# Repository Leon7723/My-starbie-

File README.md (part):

this is my first hardware proyect, im making a desktop pet or something like a tamagothi and is looking pretty good, im making this proyect for half life in hackclub my goal is to win that 3d printer but my number 1 goal is to learn how to make hardware proyects by my own :D

here is the files than i made:
{
  "board": {
    "3dviewports": [],
    "design_settings": {
      "defaults": {
        "apply_defaults_to_fp_barcodes": false,
        "apply_defaults_to_fp_dimensions": false,
        "apply_defaults_to_fp_fields": false,
        "apply_defaults_to_fp_shapes": false,
        "apply_defaults_to_fp_text": false,
        "board_outline_line_width": 0.05,
        "copper_line_width": 0.2,
        "copper_text_italic": false,
        "copper_text_size_h": 1.5,
        "copper_text_size_v": 1.5,
        "copper_text_thickness": 0.3,
        "copper_text_upright": false,
        "courtyard_line_width": 0.05,
        "dimension_precision": 4,
        "dimension_units": 3,
        "dimensions": {
          "arrow_length": 1270000,
          "extension_offset": 500000,
          "keep_text_aligned": true,
          "suppress_zeroes": true,
          "text_position": 0,
          "units_format": 0
        },
        "fab_line_width": 0.1,
        "fab_text_italic": false,
        "fab_text_size_h": 1.0,
        "fab_text_size_v": 1.0,
        "fab_text_thickness": 0.15,
        "fab_text_upright": false,
        "other_line_width": 0.1,
        "other_text_italic": false,
        "other_text_size_h": 1.0,
        "other_text_size_v": 1.0,
        "other_text_thickness": 0.15,
        "other_text_upright": false,
        "pads": {
          "drill": 0.8,
          "height": 1.27,
          "width": 1.27
        },
        "silk_line_width": 0.1,
        "silk_text_italic": false,
        "silk_text_size_h": 1.0,
        "silk_text_size_v": 1.0,
        "silk_text_thickness": 0.1,
        "silk_text_upright": false,
        "zones": {
          "border_display_style": 2,
          "border_hatch_pitch": 0.5,
          "corner_radius": 0.0,
          "corner_smoothing": 0,
          "fill_mode": 0,
          "hatch_gap": 1.5,
          "hatch_orientation": 0.0,
          "hatch_smoothing_level": 0,
          "hatch_smoothing_value": 0.1,
          "hatch_thickness": 1.0,
          "min_clearance": 0.5,
          "min_island_area": 10.0,
          "min_thickness": 0.25,
          "pad_connection": 1,
          "remove_islands": 0,
          "thermal_relief_gap": 0.5,
          "thermal_relief_spoke_width": 0.5
        }
      },
      "diff_pair_dimensions": [],
      "drc_exclusions": [],
      "meta": {
        "version": 2
      },
      "rule_severities": {
        "annular_width": "error",
        "clearance": "error",
        "connection_width": "warning",
        "copper_edge_clearance": "error",
        "copper_sliver": "warning",
        "courtyards_overlap": "error",
        "creepage": "error",
        "diff_pair_gap_out_of_range": "error",
        "diff_pair_uncoupled_length_too_long": "error",
        "drill_out_of_range": "error",
        "duplicate_footprints": "warning",
        "extra_footprint": "warning",
        "footprint": "error",
        "footprint_filters_mismatch": "ignore",
        "footprint_symbol_field_mismatch": "warning",
        "footprint_symbol_mismatch": "warning",
        "footprint_type_mismatch": "ignore",
        "hole_clearance": "error",
        "hole_to_hole": "warning",
        "holes_co_located": "warning",
        "invalid_outline": "error",
        "isolated_copper": "warning",
        "item_on_disabled_layer": "error",
        "items_not_allowed": "error",
        "length_out_of_range": "error",
        "lib_footprint_issues": "warning",
        "lib_footprint_mismatch": "warning",
        "malformed_courtyard": "error",
        "microvia_drill_out_of_range": "error",
        "mirrored_text_on_front_layer": "warning",
        "missing_courtyard": "ignore",
        "missing_footprint": "warning",
        "missing_tuning_profile": "warning",
        "net_conflict": "warning",
        "nonmirrored_text_on_back_layer": "warning",
        "npth_inside_courtyard": "error",
        "padstack": "warning",
        "pth_inside_courtyard": "error",
        "shorting_items": "error",
        "silk_edge_clearance": "warning",
        "silk_over_copper": "warning",
        "silk_overlap": "warning",
        "skew_out_of_range": "error",
        "solder_mask_bridge": "error",
        "starved_thermal": "error",
        "text_height": "warning",
        "text_on_edge_cuts": "error",
        "text_thickness": "warning",
        "through_hole_pad_without_hole": "error",
        "too_many_vias": "error",
        "track_angle": "error",
        "track_dangling": "warning",
        "track_not_centered_on_via": "ignore",
        "track_on_post_machined_layer": "error",
        "track_segment_length": "error",
        "track_width": "error",
        "tracks_crossing": "error",
        "tuning_profile_track_geometries": "ignore",
        "unconnected_items": "error",
        "unresolved_variable": "error",
        "via_dangling": "warning",
        "zones_intersect": "error"
      },
      "rules": {
        "max_error": 0.005,
        "min_clearance": 0.0,
        "min_connection": 0.0,
        "min_copper_edge_clearance": 0.5,
        "min_groove_width": 0.0,
        "min_hole_clearance": 0.25,
        "min_hole_to_hole": 0.25,
        "min_microvia_diameter": 0.2,
        "min_microvia_drill": 0.1,
        "min_resolved_spokes": 2,
        "min_silk_clearance": 0.0,
        "min_text_height": 0.8,
        "min_text_thickness": 0.08,
        "min_through_hole_diameter": 0.3,
        "min_track_width": 0.2,
        "min_via_annular_width": 0.1,
        "min_via_diameter": 0.5,
        "solder_mask_to_copper_clearance": 0.0,
        "use_height_for_length_calcs": true
      },
      "teardrop_options": [
        {
          "td_onpthpad": true,
          "td_onroundshapesonly": false,
          "td_onsmdpad": true,
          "td_ontrackend": false,
          "td_onvia": true
        }
      ],
      "teardrop_parameters": [
        {
          "td_allow_use_two_tracks": true,
          "td_curve_segcount": 0,
          "td_height_ratio": 1.0,
          "td_length_ratio": 0.5,
          "td_maxheight": 2.0,
          "td_maxlen": 1.0,
          "td_on_pad_in_zone": false,
          "td_target_name": "td_round_shape",
          "td_width_to_size_filter_ratio": 0.9
        },
        {
          "td_allow_use_two_tracks": true,
          "td_curve_segcount": 0,
          "td_height_ratio": 1.0,
          "td_length_ratio": 0.5,
          "td_maxheight": 2.0,
          "td_maxlen": 1.0,
          "td_on_pad_in_zone": false,
          "td_target_name": "td_rect_shape",
          "td_width_to_size_filter_ratio": 0.9
        },
        {
          "td_allow_use_two_tracks": true,
          "td_curve_segcount": 0,
          "td_height_ratio": 1.0,
          "td_length_ratio": 0.5,
          "td_maxheight": 2.0,
          "td_maxlen": 1.0,
          "td_on_pad_in_zone": false,
          "td_target_name": "td_track_end",
          "td_width_to_size_filter_ratio": 0.9
        }
      ],
      "track_widths": [],
      "tuning_pattern_settings": {
        "diff_pair_defaults": {
          "corner_radius_percentage": 80,
          "corner_style": 1,
          "max_amplitude": 1.0,
          "min_amplitude": 0.2,
          "single_sided": false,
          "spacing": 1.0
        },
        "diff_pair_skew_defaults": {
          "corner_radius_percentage": 80,
          "corner_style": 1,
          "max_amplitude": 1.0,
          "min_amplitude": 0.2,
          "single_sided": false,
          "spacing": 0.6
        },
        "single_track_defaults": {
          "corner_radius_percentage": 80,
          "corner_style": 1,
          "max_amplitude": 1.0,
          "min_amplitude": 0.2,
          "single_sided": false,
          "spacing": 0.6
        }
      },
      "via_dimensions": [],
      "zones_allow_external_fillets": false
    },
    "ipc2581": {
      "bom_rev": "",
      "dist": "",
      "distpn": "",
      "internal_id": "",
      "mfg": "",
      "mpn": "",
      "sch_revision": ""
    },
    "layer_pairs": [],
    "layer_presets": [],
    "viewports": []
  },
  "boards": [],
  "component_class_settings": {
    "assignments": [],
    "meta": {
      "version": 0
    },
    "sheet_component_classes": {
      "enabled": false
    }
  },
  "cvpcb": {
    "equivalence_files": []
  },
  "erc": {
    "erc_exclusions": [],
    "meta": {
      "version": 0
    },
    "pin_map": [
      [
        0,
        0,
        0,
        0,
        0,
        0,
        1,
        0,
        0,
        0,
        0,
        2
      ],
      [
        0,
        2,
        0,
        1,
        0,
        0,
        1,
        0,
        2,
        2,
        2,
        2
      ],
      [
        0,
        0,
        0,
        0,
        0,
        0,
        1,
        0,
        1,
        0,
        1,
        2
      ],
      [
        0,
        1,
        0,
        0,
        0,
        0,
        1,
        1,
        2,
        1,
        1,
        2
      ],
      [
        0,
        0,
        0,
        0,
        0,
        0,
        1,
        0,
        0,
        0,
        0,
        2
      ],
      [
        0,
        0,
        0,
        0,
        0,
        0,
        0,
        0,
        0,
        0,
        0,
        2
      ],
      [
        1,
        1,
        1,
        1,
        1,
        0,
        1,
        1,
        1,
        1,
        1,
        2
      ],
      [
        0,
        0,
        0,
        1,
        0,
        0,
        1,
        0,
        0,
        0,
        0,
        2
      ],
      [
        0,
        2,
        1,
        2,
        0,
        0,
        1,
        0,
        2,
        2,
        2,
        2
      ],
      [
        0,
        2,
        0,
        1,
        0,
        0,
        1,
        0,
        2,
        0,
        0,
        2
      ],
      [
        0,
        2,
        1,
        1,
        0,
        0,
        1,
        0,
        2,
        0,
        0,
        2
      ],
      [
        2,
        2,
        2,
        2,
        2,
        2,
        2,
        2,
        2,
        2,
        2,
        2
      ]
    ],
    "rule_severities": {
      "bus_definition_conflict": "error",
      "bus_entry_needed": "error",
      "bus_to_bus_conflict": "error",
      "bus_to_net_conflict": "error",
      "different_unit_footprint": "error",
      "different_unit_net": "error",
      "duplicate_reference": "error",
      "duplicate_sheet_names": "error",
      "endpoint_off_grid": "warning",
      "extra_units": "error",
      "field_name_whitespace": "warning",
      "footprint_filter": "ignore",
      "footprint_link_issues": "warning",
      "four_way_junction": "ignore",
      "ground_pin_not_ground": "warning",
      "hier_label_mismatch": "error",
      "isolated_pin_label": "warning",
      "label_dangling": "error",
      "label_multiple_wires": "warning",
      "lib_symbol_issues": "warning",
      "lib_symbol_mismatch": "warning",
      "missing_bidi_pin": "warning",
      "missing_input_pin": "warning",
      "missing_power_pin": "error",
      "missing_unit": "warning",
      "multiple_net_names": "warning",
      "net_not_bus_member": "warning",
      "no_connect_connected": "warning",
      "no_connect_dangling": "warning",
      "pin_not_connected": "error",
      "pin_not_driven": "error",
      "pin_to_pin": "warning",
      "power_pin_not_driven": "error",
      "same_local_global_label": "warning",
      "similar_label_and_power": "warning",
      "similar_labels": "warning",
      "similar_power": "warning",
      "simulation_model_issue": "ignore",
      "single_global_label": "ignore",
      "stacked_pin_name": "warning",
      "unannotated": "error",
      "unconnected_wire_endpoint": "warning",
      "undefined_netclass": "error",
      "unit_value_mismatch": "error",
      "unresolved_variable": "error",
      "wire_dangling": "error"
    }
  },
  "libraries": {
    "pinned_footprint_libs": [],
    "pinned_symbol_libs": []
  },
  "meta": {
    "filename": "starbie.kicad_pro",
    "version": 3
  },
  "net_settings": {
    "classes": [
      {
        "bus_width": 12,
        "clearance": 0.2,
        "diff_pair_gap": 0.25,
        "diff_pair_via_gap": 0.25,
        "diff_pair_width": 0.2,
        "line_style": 0,
        "microvia_diameter": 0.3,
        "microvia_drill": 0.1,
        "name": "Default",
        "pcb_color": "rgba(0, 0, 0, 0.000)",
        "priority": 2147483647,
        "schematic_color": "rgba(0, 0, 0, 0.000)",
        "track_width": 0.2,
        "tuning_profile": "",
        "via_diameter": 0.6,
        "via_drill": 0.3,
        "wire_width": 6
      }
    ],
    "meta": {
      "version": 5
    },
    "net_colors": null,
    "netclass_assignments": null,
    "netclass_patterns": []
  },
  "pcbnew": {
    "last_paths": {
      "idf": "",
      "netlist": "",
      "plot": "",
      "specctra_dsn": "",
      "step": "",
      "vrml": ""
    },
    "page_layout_descr_file": ""
  },
  "schematic": {
    "annotate_start_num": 0,
    "annotation": {
      "method": 0,
      "sort_order": 0
    },
    "bom_export_filename": "${PROJECTNAME}.csv",
    "bom_fmt_presets": [],
    "bom_fmt_settings": {
      "field_delimiter": ",",
      "keep_line_breaks": false,
      "keep_tabs": false,
      "name": "CSV",
      "ref_delimiter": ",",
      "ref_range_delimiter": "",
      "string_delimiter": "\""
    },
    "bom_presets": [],
    "bom_settings": {
      "exclude_dnp": false,
      "fields_ordered": [
        {
          "group_by": false,
          "label": "Reference",
          "name": "Reference",
          "show": true
        },
        {
          "group_by": false,
          "label": "Qty",
          "name": "${QUANTITY}",
          "show": true
        },
        {
          "group_by": true,
          "label": "Value",
          "name": "Value",
          "show": true
        },
        {
          "group_by": true,
          "label": "DNP",
          "name": "${DNP}",
          "show": true
        },
        {
          "group_by": true,
          "label": "Exclude from BOM",
          "name": "${EXCLUDE_FROM_BOM}",
          "show": true
        },
        {
          "group_by": true,
          "label": "Exclude from Board",
          "name": "${EXCLUDE_FROM_BOARD}",
          "show": true
        },
        {
          "group_by": true,
          "label": "Exclude from Simulation",
          "name": "${EXCLUDE_FROM_SIM}",
          "show": true
        },
        {
          "group_by": true,
          "label": "Exclude from Position Files",
          "name": "${EXCLUDE_FROM_POS_FILES}",
          "show": true
        },
        {
          "group_by": true,
          "label": "Footprint",
          "name": "Footprint",
          "show": true
        },
        {
          "group_by": false,
          "label": "Datasheet",
          "name": "Datasheet",
          "show": true
        }
      ],
      "filter_string": "",
      "group_symbols": true,
      "include_excluded_from_bom": true,
      "name": "Default Editing",
      "sort_asc": true,
      "sort_field": "Reference"
    },
    "bus_aliases": {},
    "connection_grid_size": 50.0,
    "drawing": {
      "dashed_lines_dash_length_ratio": 12.0,
      "dashed_lines_gap_length_ratio": 3.0,
      "default_line_thickness": 6.0,
      "default_text_size": 50.0,
      "field_names": [],
      "hop_over_size_choice": 0,
      "intersheets_ref_own_page": false,
      "intersheets_ref_prefix": "",
      "intersheets_ref_short": false,
      "intersheets_ref_show": false,
      "intersheets_ref_suffix": "",
      "junction_size_choice": 3,
      "label_size_ratio": 0.375,
      "operating_point_overlay_i_precision": 3,
      "operating_point_overlay_i_range": "~A",
      "operating_point_overlay_v_precision": 3,
      "operating_point_overlay_v_range": "~V",
      "overbar_offset_ratio": 1.23,
      "pin_symbol_size": 25.0,
      "text_offset_ratio": 0.15
    },
    "legacy_lib_dir": "",
    "legacy_lib_list": [],
    "meta": {
      "version": 1
    },
    "page_layout_descr_file": "",
    "plot_directory": "",
    "reuse_designators": true,
    "subpart_first_id": 65,
    "subpart_id_separator": 0,
    "top_level_sheets": [
      {
        "filename": "starbie.kicad_sch",
        "name": "Root",
        "uuid": "8977db72-0acb-4ad4-afa3-dd83609eab31"
      }
    ],
    "used_designators": "U1-2,SW1-2,R1,J1-2,#PWR1-13",
    "variants": []
  },
  "sheets": [
    [
      "8977db72-0acb-4ad4-afa3-dd83609eab31",
      "Root"
    ]
  ],
  "text_variables": {},
  "tuning_profiles": {
    "meta": {
      "version": 0
    },
    "tuning_profiles_impedance_geometric": []
  }
}

(kicad_pcb
	(version 20260206)
	(generator "pcbnew")
	(generator_version "10.0")
	(general
		(thickness 1.6)
		(legacy_teardrops no)
	)
	(paper "A4")
	(layers
		(0 "F.Cu" signal)
		(2 "B.Cu" signal)
		(9 "F.Adhes" user "F.Adhesive")
		(11 "B.Adhes" user "B.Adhesive")
		(13 "F.Paste" user)
		(15 "B.Paste" user)
		(5 "F.SilkS" user "F.Silkscreen")
		(7 "B.SilkS" user "B.Silkscreen")
		(1 "F.Mask" user)
		(3 "B.Mask" user)
		(17 "Dwgs.User" user "User.Drawings")
		(19 "Cmts.User" user "User.Comments")
		(21 "Eco1.User" user "User.Eco1")
		(23 "Eco2.User" user "User.Eco2")
		(25 "Edge.Cuts" user)
		(27 "Margin" user)
		(31 "F.CrtYd" user "F.Courtyard")
		(29 "B.CrtYd" user "B.Courtyard")
		(35 "F.Fab" user)
		(33 "B.Fab" user)
		(39 "User.1" user)
		(41 "User.2" user)
		(43 "User.3" user)
		(45 "User.4" user)
	)
	(setup
		(pad_to_mask_clearance 0)
		(allow_soldermask_bridges_in_footprints no)
		(tenting
			(front yes)
			(back yes)
		)
		(covering
			(front no)
			(back no)
		)
		(plugging
			(front no)
			(back no)
		)
		(capping no)
		(filling no)
		(pcbplotparams
			(layerselection 0x00000000_00000000_55555555_5755f5ff)
			(plot_on_all_layers_selection 0x00000000_00000000_00000000_00000000)
			(disableapertmacros no)
			(usegerberextensions no)
			(usegerberattributes yes)
			(usegerberadvancedattributes yes)
			(creategerberjobfile yes)
			(dashed_line_dash_ratio 12)
			(dashed_line_gap_ratio 3)
			(svgprecision 4)
			(plotframeref no)
			(mode 1)
			(useauxorigin no)
			(pdf_front_fp_property_popups yes)
			(pdf_back_fp_property_popups yes)
			(pdf_metadata yes)
			(pdf_single_document no)
			(dxfpolygonmode yes)
			(dxfimperialunits yes)
			(dxfusepcbnewfont yes)
			(psnegative no)
			(psa4output no)
			(plot_black_and_white yes)
			(sketchpadsonfab no)
			(plotpadnumbers no)
			(hidednponfab no)
			(sketchdnponfab yes)
			(crossoutdnponfab yes)
			(subtractmaskfromsilk no)
			(outputformat 1)
			(mirror no)
			(drillshape 1)
			(scaleselection 1)
			(outputdirectory "")
		)
	)
	(footprint "Button_Switch_Keyboard:SW_Cherry_MX_1.00u_PCB"
		(layer "F.Cu")
		(uuid "04947574-7416-4cc5-8b59-ddabbcdf914b")
		(at 125.96 61.42)
		(descr "Cherry MX keyswitch, 1.00u, PCB mount, http://cherryamericas.com/wp-content/uploads/2014/12/mx_cat.pdf")
		(tags "Cherry MX keyswitch 1.00u PCB")
		(property "Reference" "SW1"
			(at -2.54 -2.794 0)
			(layer "F.SilkS")
			(uuid "132addf6-2cf2-4cc4-88fb-be52d615f856")
			(effects
				(font
					(size 1 1)
					(thickness 0.15)
				)
			)
		)
		(property "Value" "SW_Push"
			(at -2.54 12.954 0)
			(layer "F.Fab")
			(uuid "f20ce212-0395-475c-ab5a-2ed35deecf76")
			(effects
				(font
					(size 1 1)
					(thickness 0.15)
				)
			)
		)
		(property "Datasheet" ""
			(at 0 0 0)
			(unlocked yes)
			(layer "F.Fab")
			(hide yes)
			(uuid "22c549e9-61a7-43be-9221-d960f5cf3cf2")
			(effects
				(font
					(size 1.27 1.27)
					(thickness 0.15)
				)
			)
		)
		(property "Description" "Push button switch, generic, two pins"
			(at 0 0 0)
			(unlocked yes)
			(layer "F.Fab")
			(hide yes)
			(uuid "7d2f7fe1-6565-423b-a553-d9594f436d74")
			(effects
				(font
					(size 1.27 1.27)
					(thickness 0.15)
				)
			)
		)
		(path "/6c2d0e86-b1ff-40f8-8c9f-153c65c3ee15")
		(sheetname "/")
		(sheetfile "starbie.kicad_sch")
		(units
			(unit
				(name "A")
				(pins "1" "2")
			)
		)
		(attr through_hole)
		(duplicate_pad_numbers_are_jumpers no)
		(fp_line
			(start -9.525 -1.905)
			(end 4.445 -1.905)
			(stroke
				(width 0.12)
				(type solid)
			)
			(layer "F.SilkS")
			(uuid "a28ee2ab-d00a-4bbe-a005-b5f784556526")
		)
		(fp_line
			(start -9.525 12.065)
			(end -9.525 -1.905)
			(stroke
				(width 0.12)
				(type solid)
			)
			(layer "F.SilkS")
			(uuid "6eea82b2-2c50-4da5-b7d3-b83acb185266")
		)
		(fp_line
			(start 4.445 -1.905)
			(end 4.445 12.065)
			(stroke
				(width 0.12)
				(type solid)
			)
			(layer "F.SilkS")
			(uuid "b50e151d-3af0-442f-9106-87fc13568458")
		)
		(fp_line
			(start 4.445 12.065)
			(end -9.525 12.065)
			(stroke
				(width 0.12)
				(type solid)
			)
			(layer "F.SilkS")
			(uuid "75a63ca7-dc22-4e55-95bc-e4980ed241a7")
		)
		(fp_line
			(start -12.065 -4.445)
			(end 6.985 -4.445)
			(stroke
				(width 0.15)
				(type solid)
			)
			(layer "Dwgs.User")
			(uuid "a4316273-7a1b-420c-a8fc-29acb0b7fac4")
		)
		(fp_line
			(start -12.065 14.605)
			(end -12.065 -4.445)
			(stroke
				(width 0.15)
				(type solid)
			)
			(layer "Dwgs.User")
			(uuid "78c734cc-3ac1-4bcd-8f04-a0f06144b939")
		)
		(fp_line
			(start 6.985 -4.445)
			(end 6.985 14.605)
			(stroke
				(width 0.15)
				(type solid)
			)
			(layer "Dwgs.User")
			(uuid "d065de42-0f82-4f18-80ed-cecb038134eb")
		)
		(fp_line
			(start 6.985 14.605)
			(end -12.065 14.605)
			(stroke
				(width 0.15)
				(type solid)
			)
			(layer "Dwgs.User")
			(uuid "ddfaa2da-c5e8-4b48-80f8-5292d8794895")
		)
		(fp_line
			(start -9.14 -1.52)
			(end 4.06 -1.52)
			(stroke
				(width 0.05)
				(type solid)
			)
			(layer "F.CrtYd")
			(uuid "9c98e6c3-9128-4f0e-b70b-2670f6951c46")
		)
		(fp_line
			(start -9.14 11.68)
			(end -9.14 -1.52)
			(stroke
				(width 0.05)
				(type solid)
			)
			(layer "F.CrtYd")
			(uuid "39c0d82c-ac3e-4125-89c2-3e9910a38456")
		)
		(fp_line
			(start 4.06 -1.52)
			(end 4.06 11.68)
			(stroke
				(width 0.05)
				(type solid)
			)
			(layer "F.CrtYd")
			(uuid "b3e67ae2-3ecd-4883-a7f6-076ef99d186b")
		)
		(fp_line
			(start 4.06 11.68)
			(end -9.14 11.68)
			(stroke
				(width 0.05)
				(type solid)
			)
			(layer "F.CrtYd")
			(uuid "a4c458d3-c2e1-4908-849c-2d97809b41e4")
		)
		(fp_line
			(start -8.89 -1.27)
			(end 3.81 -1.27)
			(stroke
				(width 0.1)
				(type solid)
			)
			(layer "F.Fab")
			(uuid "18de7187-ac3b-49d3-a1f6-a358b98e4163")
		)
		(fp_line
			(start -8.89 11.43)
			(end -8.89 -1.27)
			(stroke
				(width 0.1)
				(type solid)
			)
			(layer "F.Fab")
			(uuid "33423380-56ce-4d9c-a48a-4f5b19c81899")
		)
		(fp_line
			(start 3.81 -1.27)
			(end 3.81 11.43)
			(stroke
				(width 0.1)
				(type solid)
			)
			(layer "F.Fab")
			(uuid "1b672b95-718c-470c-9bc7-e3b12f699fa5")
		)
		(fp_line
			(start 3.81 11.43)
			(end -8.89 11.43)
			(stroke
				(width 0.1)
				(type solid)
			)
			(layer "F.Fab")
			(uuid "b3a7395a-ab9d-47c4-adad-9ad8906270ee")
		)
		(fp_text user "${REFERENCE}"
			(at -2.54 -2.794 0)
			(layer "F.Fab")
			(uuid "7bf67fcc-76aa-45bc-806b-e6e624cb3fed")
			(effects
				(font
					(size 1 1)
					(thickness 0.15)
				)
			)
		)
		(pad "" np_thru_hole circle
			(at -7.62 5.08)
			(size 1.7 1.7)
			(drill 1.7)
			(layers "*.Cu" "*.Mask")
			(uuid "2e3083d1-e926-470d-80b4-f84540161596")
		)
		(pad "" np_thru_hole circle
			(at -2.54 5.08)
			(size 4 4)
			(drill 4)
			(layers "*.Cu" "*.Mask")
			(uuid "16aa3495-d0af-4f73-a243-1d8c19ad124a")
		)
		(pad "" np_thru_hole circle
			(at 2.54 5.08)
			(size 1.7 1.7)
			(drill 1.7)
			(layers "*.Cu" "*.Mask")
			(uuid "94529e87-416b-46bd-9648-98cffbd182bb")
		)
		(pad "1" thru_hole circle
			(at 0 0)
			(size 2.2 2.2)
			(drill 1.5)
			(layers "*.Cu" "*.Mask")
			(remove_unused_layers no)
			(net "/GPIO2")
			(pinfunction "1_1")
			(pintype "passive")
			(uuid "81945a4a-24d3-4cf3-a907-b8f6f99d8b53")
		)
		(pad "2" thru_hole circle
			(at -6.35 2.54)
			(size 2.2 2.2)
			(drill 1.5)
			(layers "*.Cu" "*.Mask")
			(remove_unused_layers no)
			(net "GND")
			(pinfunction "2_2")
			(pintype "passive")
			(uuid "61a55750-5a8b-4cbe-ae89-f1ca6d92014f")
		)
		(embedded_fonts no)
		(model "${KICAD10_3DMODEL_DIR}/Button_Switch_Keyboard.3dshapes/SW_Cherry_MX_1.00u_PCB.step"
			(offset
				(xyz 0 0 0)
			)
			(scale
				(xyz 1 1 1)
			)
			(rotate
				(xyz 0 0 0)
			)
		)
	)
	(footprint "Imported Parts:gordo"
		(layer "F.Cu")
		(uuid "33e2cf77-acd5-4f6c-93fb-80336e71239e")
		(at 171 94)
		(property "Reference" "G***"
			(at 0 0 0)
			(layer "F.SilkS")
			(hide yes)
			(uuid "f2af4785-8d11-428b-bd13-a065e775ce92")
			(effects
				(font
					(size 1.5 1.5)
					(thickness 0.3)
				)
			)
		)
		(property "Value" "LOGO"
			(at 0.75 0 0)
			(layer "F.SilkS")
			(hide yes)
			(uuid "96da0eb3-15b9-4ff6-839d-97fa82bd7b2d")
			(effects
				(font
					(size 1.5 1.5)
					(thickness 0.3)
				)
			)
		)
		(property "Datasheet" ""
			(at 0 0 0)
			(layer "F.Fab")
			(hide yes)
			(uuid "f6288957-4141-4291-8eed-809600e34958")
			(effects
				(font
					(size 1.27 1.27)
				)
			)
		)
		(property "Description" ""
			(at 0 0 0)
			(layer "F.Fab")
			(hide yes)
			(uuid "cced8284-b5f3-4d53-8bec-fe6f4cc8d6fc")
			(effects
				(font
					(size 1.27 1.27)
				)
			)
		)
		(attr board_only exclude_from_pos_files exclude_from_bom)
		(duplicate_pad_numbers_are_jumpers no)
		(fp_poly
			(pts
				(xy -3.913965 3.703317) (xy -3.92076 3.710112) (xy -3.927555 3.703317) (xy -3.92076 3.696522)
			)
			(stroke
				(width 0)
				(type solid)
			)
			(fill yes)
			(layer "F.Cu")
			(uuid "ee6b24d8-ce97-411f-9524-1027a0ce483d")
		)
		(fp_poly
			(pts
				(xy 1.861851 -2.656876) (xy 1.855056 -2.650081) (xy 1.848261 -2.656876) (xy 1.855056 -2.663671)
			)
			(stroke
				(width 0)
				(type solid)
			)
			(fill yes)
			(layer "F.Cu")
			(uuid "940d88bf-86ee-4ffd-aa98-fb7fa2bfcb02")
		)
		(fp_poly
			(pts
				(xy 3.723702 -0.169877) (xy 3.716907 -0.163082) (xy 3.710112 -0.169877) (xy 3.716907 -0.176672)
			)
			(stroke
				(width 0)
				(type solid)
			)
			(fill yes)
			(layer "F.Cu")
			(uuid "aa6534fd-0291-4f2f-a90f-0eb1d45138a5")
		)
		(fp_poly
			(pts
				(xy 3.177503 -4.219443) (xy 3.180096 -4.212949) (xy 3.170342 -4.199747) (xy 3.167308 -4.199358)
				(xy 3.148902 -4.209237) (xy 3.146121 -4.212949) (xy 3.149201 -4.224583) (xy 3.158909 -4.226539)
			)
			(stroke
				(width 0)
				(type solid)
			)
			(fill yes)
			(layer "F.Cu")
			(uuid "6ac66d85-038d-4bea-909f-345af4021f24")
		)
		(fp_poly
			(pts
				(xy -0.713788 2.828456) (xy -0.707868 2.85656) (xy -0.706688 2.896968) (xy -0.708331 2.937096) (xy -0.714982 2.95676)
				(xy -0.729232 2.962568) (xy -0.732415 2.962653) (xy -0.757954 2.952662) (xy -0.76639 2.941157) (xy -0.7748 2.896722)
				(xy -0.768141 2.856303) (xy -0.748924 2.830821) (xy -0.72673 2.821041)
			)
			(stroke
				(width 0)
				(type solid)
			)
			(fill yes)
			(layer "F.Cu")
			(uuid "bb9973cd-3411-4fe2-9ed2-4958b926a865")
		)
		(fp_poly
			(pts
				(xy 1.416093 -1.647476) (xy 1.429872 -1.638467) (xy 1.446422 -1.623444) (xy 1.44358 -1.617229) (xy 1.428862 -1.606273)
				(xy 1.426966 -1.596844) (xy 1.415152 -1.580448) (xy 1.392991 -1.576458) (xy 1.365337 -1.583798)
				(xy 1.359015 -1.597814) (xy 1.368048 -1.624598) (xy 1.379283 -1.639438) (xy 1.397137 -1.652284)
			)
			(stroke
				(width 0)
				(type solid)
			)
			(fill yes)
			(layer "F.Cu")
			(uuid "96b8f6a7-0a04-4635-913e-03ad24b825ca")
		)
		(fp_poly
			(pts
				(xy -0.808096 -0.699711) (xy -0.801664 -0.681805) (xy -0.815417 -0.65751) (xy -0.848273 -0.631366)
				(xy -0.854633 -0.62765) (xy -0.893288 -0.606859) (xy -0.914073 -0.600347) (xy -0.922512 -0.608556)
				(xy -0.92413 -0.631928) (xy -0.924131 -0.633215) (xy -0.915042 -0.664766) (xy -0.896951 -0.67557)
				(xy -0.874919 -0.686327) (xy -0.86977 -0.694683) (xy -0.858131 -0.703711) (xy -0.835795 -0.706688)
			)
			(stroke
				(width 0)
				(type solid)
			)
			(fill yes)
			(layer "F.Cu")
			(uuid "0ce9dda8-c7e6-460b-9959-674bda48d417")
		)
		(fp_poly
			(pts
				(xy 2.090766 -3.317917) (xy 2.098544 -3.307258) (xy 2.104068 -3.286786) (xy 2.103396 -3.281906)
				(xy 2.090702 -3.273592) (xy 2.062588 -3.255835) (xy 2.043976 -3.244208) (xy 2.009916 -3.224066)
				(xy 1.990235 -3.217712) (xy 1.976584 -3.224024) (xy 1.967401 -3.233907) (xy 1.954195 -3.254209)
				(xy 1.961381 -3.270351) (xy 1.972296 -3.280346) (xy 2.000064 -3.297582) (xy 2.018293 -3.302408)
				(xy 2.036278 -3.309795) (xy 2.038523 -3.315998) (xy 2.048259 -3.328169) (xy 2.069605 -3.328236)
			)
			(stroke
				(width 0)
				(type solid)
			)
			(fill yes)
			(layer "F.Cu")
			(uuid "67c1086f-8bec-486d-80cb-244f400202a2")
		)
		(fp_poly
			(pts
				(xy -0.594646 2.939541) (xy -0.585309 2.957337) (xy -0.584377 2.976244) (xy -0.580441 3.00487) (xy -0.570956 3.017011)
				(xy -0.570787 3.017014) (xy -0.561804 3.028961) (xy -0.557314 3.058337) (xy -0.557197 3.06458) (xy -0.560202 3.097312)
				(xy -0.572025 3.11054) (xy -0.584713 3.112145) (xy -0.611785 3.099633) (xy -0.625451 3.077372) (xy -0.636516 3.040241)
				(xy -0.646236 2.995013) (xy -0.647237 2.989036) (xy -0.651388 2.954743) (xy -0.646431 2.939472)
				(xy -0.628488 2.93557) (xy -0.620089 2.935473)
			)
			(stroke
				(width 0)
				(type solid)
			)
			(fill yes)
			(layer "F.Cu")
			(uuid "43cf1de7-6092-411c-ad36-10b485ba398e")
		)
		(fp_poly
			(pts
				(xy 1.972187 -3.445745) (xy 1.977493 -3.42309) (xy 1.977424 -3.422098) (xy 1.969279 -3.396135) (xy 1.95931 -3.38699)
				(xy 1.944753 -3.370654) (xy 1.943392 -3.362431) (xy 1.935681 -3.345085) (xy 1.929802 -3.343179)
				(xy 1.916902 -3.332611) (xy 1.916211 -3.327772) (xy 1.906972 -3.31094) (xy 1.885141 -3.286604) (xy 1.859552 -3.263326)
				(xy 1.839038 -3.249666) (xy 1.834671 -3.248744) (xy 1.820664 -3.257907) (xy 1.812616 -3.265715)
				(xy 1.809176 -3.288978) (xy 1.82828 -3.327186) (xy 1.869855 -3.380207) (xy 1.885248 -3.3974) (xy 1.906336 -3.423229)
				(xy 1.916126 -3.440706) (xy 1.916211 -3.441568) (xy 1.927789 -3.449536) (xy 1.947916 -3.4519)
			)
			(stroke
				(width 0)
				(type solid)
			)
			(fill yes)
			(layer "F.Cu")
			(uuid "a1d19e45-e728-430a-ace8-de5468ba469c")
		)
		(fp_poly
			(pts
				(xy -1.419322 0.964449) (xy -1.413685 0.967862) (xy -1.401888 0.977468) (xy -1.394033 0.992143)
				(xy -1.389331 1.016959) (xy -1.386994 1.056988) (xy -1.386235 1.117302) (xy -1.386196 1.144842)
				(xy -1.385193 1.208053) (xy -1.38245 1.259155) (xy -1.37837 1.293046) (xy -1.373605 1.304654) (xy -1.367099 1.317182)
				(xy -1.360751 1.350545) (xy -1.355646 1.398414) (xy -1.354392 1.416773) (xy -1.349378 1.481662)
				(xy -1.342389 1.547307) (xy -1.334869 1.600296) (xy -1.334279 1.603638) (xy -1.316165 1.699251)
				(xy -1.30046 1.772366) (xy -1.287484 1.821681) (xy -1.277555 1.845891) (xy -1.274366 1.848261) (xy -1.267801 1.860324)
				(xy -1.264151 1.890458) (xy -1.263885 1.902621) (xy -1.260871 1.936662) (xy -1.253341 1.955596)
				(xy -1.250295 1.956982) (xy -1.239703 1.968498) (xy -1.236744 1.98756) (xy -1.231715 2.014218) (xy -1.21851 2.057686)
				(xy -1.20001 2.109947) (xy -1.179095 2.16298) (xy -1.158647 2.208767) (xy -1.153807 2.218408) (xy -1.143246 2.249001)
				(xy -1.141573 2.262576) (xy -1.134292 2.280779) (xy -1.127983 2.283146) (xy -1.117767 2.294776)
				(xy -1.114393 2.317121) (xy -1.110438 2.342671) (xy -1.102851 2.351096) (xy -1.091428 2.362542)
				(xy -1.075245 2.391687) (xy -1.066089 2.412252) (xy -1.049429 2.447754) (xy -1.035185 2.469818)
				(xy -1.030066 2.473408) (xy -1.021281 2.484813) (xy -1.019262 2.500588) (xy -1.013571 2.522672)
				(xy -1.005672 2.527768) (xy -0.992632 2.538237) (xy -0.992082 2.542329) (xy -0.98381 2.564038) (xy -0.975094 2.575833)
				(xy -0.942441 2.613652) (xy -0.926621 2.635878) (xy -0.924131 2.643279) (xy -0.915829 2.657888)
				(xy -0.896951 2.680391) (xy -0.877141 2.707304) (xy -0.86977 2.727388) (xy -0.858768 2.742967) (xy -0.84844 2.745211)
				(xy -0.831775 2.753974) (xy -0.830157 2.773955) (xy -0.840995 2.795691) (xy -0.861697 2.809719)
				(xy -0.866373 2.810709) (xy -0.89002 2.808494) (xy -0.896951 2.799899) (xy -0.905518 2.780244) (xy -0.926264 2.753408)
				(xy -0.927528 2.752043) (xy -0.963519 2.712339) (xy -0.983622 2.686494) (xy -0.991517 2.6695) (xy -0.992082 2.664244)
				(xy -1.002078 2.650586) (xy -1.005672 2.65008) (xy -1.016714 2.638697) (xy -1.019262 2.6229) (xy -1.024065 2.600803)
				(xy -1.030712 2.595719) (xy -1.043809 2.584875) (xy -1.0623 2.557875) (xy -1.067778 2.548154) (xy -1.086392 2.518028)
				(xy -1.101187 2.501606) (xy -1.103893 2.500588) (xy -1.112431 2.48918) (xy -1.114393 2.473408) (xy -1.120084 2.451324)
				(xy -1.127983 2.446228) (xy -1.140467 2.435419) (xy -1.141573 2.428386) (xy -1.14717 2.407004) (xy -1.161605 2.370601)
				(xy -1.175549 2.340116) (xy -1.194084 2.299469) (xy -1.206424 2.268141) (xy -1.209524 2.256032)
				(xy -1.219825 2.242782) (xy -1.223114 2.242375) (xy -1.232656 2.230566) (xy -1.236703 2.202112)
				(xy -1.236705 2.201605) (xy -1.240641 2.172978) (xy -1.250126 2.160837) (xy -1.250295 2.160834)
				(xy -1.26082 2.149293) (xy -1.263885 2.129577) (xy -1.268574 2.099329) (xy -1.275511 2.085409) (xy -1.287377 2.063239)
				(xy -1.30199 2.024315) (xy -1.316301 1.978436) (xy -1.327264 1.935405) (xy -1.331829 1.905021) (xy -1.331836 1.904267)
				(xy -1.337891 1.877901) (xy -1.345426 1.868646) (xy -1.354113 1.850827) (xy -1.358768 1.817028)
				(xy -1.359016 1.806688) (xy -1.362072 1.772945) (xy -1.369694 1.754376) (xy -1.372606 1.75313) (xy -1.380315 1.740898)
				(xy -1.38524 1.709584) (xy -1.386196 1.684285) (xy -1.388905 1.638682) (xy -1.395779 1.601099) (xy -1.400225 1.589229)
				(xy -1.408893 1.560963) (xy -1.41783 1.511091) (xy -1.42662 1.444926) (xy -1.434849 1.367785) (xy -1.442103 1.284983)
				(xy -1.447969 1.201835) (xy -1.452032 1.123658) (xy -1.453877 1.055766) (xy -1.453092 1.003474)
				(xy -1.449261 0.972099) (xy -1.448485 0.969748) (xy -1.438618 0.95781)
			)
			(stroke
				(width 0)
				(type solid)
			)
			(fill yes)
			(layer "F.Cu")
			(uuid "070d7498-ce48-47a0-b73a-378570133638")
		)
		(fp_poly
			(pts
				(xy 2.309917 -2.646419) (xy 2.329959 -2.637502) (xy 2.330711 -2.636491) (xy 2.348783 -2.6273) (xy 2.381716 -2.622953)
				(xy 2.385874 -2.6229) (xy 2.416993 -2.619433) (xy 2.432307 -2.610924) (xy 2.432637 -2.60931) (xy 2.443932 -2.598005)
				(xy 2.457917 -2.59572) (xy 2.482005 -2.586835) (xy 2.51512 -2.564207) (xy 2.53363 -2.548154) (xy 2.566304 -2.520716)
				(xy 2.593658 -2.50353) (xy 2.603482 -2.500589) (xy 2.618915 -2.494086) (xy 2.619502 -2.488683) (xy 2.626105 -2.472909)
				(xy 2.646706 -2.444826) (xy 2.667068 -2.421324) (xy 2.695273 -2.388217) (xy 2.71378 -2.361857) (xy 2.718031 -2.351505)
				(xy 2.723757 -2.328018) (xy 2.730035 -2.31354) (xy 2.75258 -2.266596) (xy 2.76698 -2.22688) (xy 2.775022 -2.185575)
				(xy 2.778493 -2.133868) (xy 2.779186 -2.071121) (xy 2.77739 -1.992621) (xy 2.771974 -1.940684) (xy 2.762897 -1.914931)
				(xy 2.762199 -1.914174) (xy 2.747246 -1.888956) (xy 2.745211 -1.877703) (xy 2.734566 -1.85457) (xy 2.708875 -1.827539)
				(xy 2.6775 -1.804665) (xy 2.649806 -1.794003) (xy 2.647815 -1.793917) (xy 2.625562 -1.786447) (xy 2.620323 -1.779376)
				(xy 2.605397 -1.770936) (xy 2.570635 -1.761865) (xy 2.523323 -1.753318) (xy 2.470746 -1.746453)
				(xy 2.420191 -1.742423) (xy 2.385072 -1.742057) (xy 2.348807 -1.744558) (xy 2.298714 -1.749269)
				(xy 2.26276 -1.753205) (xy 2.205632 -1.762617) (xy 2.154376 -1.775907) (xy 2.115273 -1.790956) (xy 2.094603 -1.805649)
				(xy 2.092883 -1.810471) (xy 2.081616 -1.819727) (xy 2.069101 -1.821597) (xy 2.048288 -1.832675)
				(xy 2.021631 -1.859666) (xy 1.995555 -1.894225) (xy 1.986979 -1.909417) (xy 2.204254 -1.909417)
				(xy 2.205723 -1.886208) (xy 2.209977 -1.884164) (xy 2.210519 -1.885376) (xy 2.213207 -1.912355)
				(xy 2.211023 -1.926146) (xy 2.206697 -1.931688) (xy 2.204344 -1.913637) (xy 2.204254 -1.909417)
				(xy 1.986979 -1.909417) (xy 1.976482 -1.928011) (xy 1.970572 -1.949567) (xy 1.962216 -1.972627)
				(xy 1.956982 -1.977368) (xy 1.949742 -1.99446) (xy 1.944813 -2.03024) (xy 1.943392 -2.067308) (xy 1.942231 -2.09402)
				(xy 2.168018 -2.09402) (xy 2.168443 -2.063176) (xy 2.173758 -2.036272) (xy 2.182693 -2.024934) (xy 2.185858 -2.037048)
				(xy 2.187522 -2.067513) (xy 2.187583 -2.079294) (xy 2.545708 -2.079294) (xy 2.546404 -2.041958)
				(xy 2.54824 -2.025334) (xy 2.550837 -2.032468) (xy 2.55119 -2.035126) (xy 2.553439 -2.08278) (xy 2.55119 -2.123462)
				(xy 2.548525 -2.133719) (xy 2.546576 -2.119844) (xy 2.54572 -2.084884) (xy 2.545708 -2.079294) (xy 2.187583 -2.079294)
				(xy 2.187601 -2.082692) (xy 2.186068 -2.116562) (xy 2.181346 -2.126266) (xy 2.173623 -2.117181)
				(xy 2.168018 -2.09402) (xy 1.942231 -2.09402) (xy 1.941371 -2.113821) (xy 1.936713 -2.133655) (xy 2.4222 -2.133655)
				(xy 2.423617 -2.10893) (xy 2.427145 -2.106016) (xy 2.428415 -2.109872) (xy 2.430529 -2.14434) (xy 2.428415 -2.157438)
				(xy 2.424476 -2.161667) (xy 2.422332 -2.142875) (xy 2.4222 -2.133655) (xy 1.936713 -2.133655) (xy 1.935661 -2.138136)
				(xy 1.929802 -2.14045) (xy 1.920225 -2.145815) (xy 1.916224 -2.172416) (xy 1.916211 -2.174425) (xy 1.91983 -2.20205)
				(xy 1.929155 -2.208761) (xy 1.929802 -2.208401) (xy 1.937539 -2.21585) (xy 1.942187 -2.247783) (xy 1.943392 -2.289324)
				(xy 1.945244 -2.339277) (xy 1.950072 -2.380625) (xy 1.95599 -2.402245) (xy 1.970893 -2.433202) (xy 1.976289 -2.446228)
				(xy 1.996179 -2.483528) (xy 2.164353 -2.483528) (xy 2.167889 -2.450573) (xy 2.169456 -2.443803)
				(xy 2.180665 -2.398663) (xy 2.185298 -2.444137) (xy 2.186365 -2.477194) (xy 2.182744 -2.49666) (xy 2.182178 -2.497365)
				(xy 2.169549 -2.50095) (xy 2.164353 -2.483528) (xy 1.996179 -2.483528) (xy 1.996797 -2.484687) (xy 2.023622 -2.520172)
				(xy 2.255965 -2.520172) (xy 2.260279 -2.49705) (xy 2.269556 -2.493794) (xy 2.280972 -2.512962) (xy 2.283034 -2.527769)
				(xy 2.326062 -2.527769) (xy 2.328198 -2.508476) (xy 2.332917 -2.510782) (xy 2.334712 -2.538605)
				(xy 2.332917 -2.544757) (xy 2.327956 -2.546464) (xy 2.326062 -2.527769) (xy 2.283034 -2.527769)
				(xy 2.283146 -2.528571) (xy 2.2773 -2.550216) (xy 2.269556 -2.55495) (xy 2.259426 -2.543295) (xy 2.255965 -2.520172)
				(xy 2.023622 -2.520172) (xy 2.027652 -2.525503) (xy 2.06257 -2.561996) (xy 2.095267 -2.587482) (xy 2.116666 -2.595503)
				(xy 2.132461 -2.604305) (xy 2.133654 -2.60931) (xy 2.145445 -2.618925) (xy 2.173622 -2.6229) (xy 2.205007 -2.62709)
				(xy 2.22199 -2.636491) (xy 2.240094 -2.645747) (xy 2.272906 -2.650043) (xy 2.276351 -2.650081)
			)
			(stroke
				(width 0)
				(type solid)
			)
			(fill yes)
			(layer "F.Cu")
			(uuid "b5677681-deed-4fa6-b162-150cce6fe40f")
		)
		(fp_poly
			(pts
				(xy 0.322892 -2.594114) (xy 0.363344 -2.589854) (xy 0.385508 -2.583778) (xy 0.387319 -2.58213) (xy 0.406448 -2.570796)
				(xy 0.42267 -2.56854) (xy 0.443379 -2.565692) (xy 0.465241 -2.55411) (xy 0.495986 -2.529238) (xy 0.509131 -2.517577)
				(xy 0.529293 -2.503182) (xy 0.536811 -2.500589) (xy 0.553405 -2.49141) (xy 0.573257 -2.471961) (xy 0.584232 -2.454376)
				(xy 0.584376 -2.453023) (xy 0.59237 -2.436707) (xy 0.601364 -2.425344) (xy 0.631503 -2.390057) (xy 0.646883 -2.366052)
				(xy 0.652072 -2.345504) (xy 0.652327 -2.338081) (xy 0.657913 -2.315688) (xy 0.665917 -2.310327)
				(xy 0.6749 -2.29838) (xy 0.67939 -2.269004) (xy 0.679507 -2.262761) (xy 0.682921 -2.231322) (xy 0.691314 -2.215607)
				(xy 0.693098 -2.215196) (xy 0.699945 -2.202548) (xy 0.704718 -2.168313) (xy 0.706675 -2.118049)
				(xy 0.706688 -2.11327) (xy 0.705001 -2.061912) (xy 0.700437 -2.026115) (xy 0.693735 -2.011439) (xy 0.693098 -2.011343)
				(xy 0.684993 -1.999197) (xy 0.680131 -1.968464) (xy 0.679507 -1.950188) (xy 0.677349 -1.913709)
				(xy 0.67189 -1.891833) (xy 0.668647 -1.889032) (xy 0.65716 -1.877641) (xy 0.64327 -1.849732) (xy 0.641397 -1.844864)
				(xy 0.623287 -1.809317) (xy 0.596089 -1.769989) (xy 0.565618 -1.733833) (xy 0.537687 -1.707801)
				(xy 0.519233 -1.69877) (xy 0.503872 -1.689924) (xy 0.502835 -1.68518) (xy 0.491953 -1.672846) (xy 0.484114 -1.671589)
				(xy 0.460297 -1.662002) (xy 0.448475 -1.651204) (xy 0.42212 -1.634951) (xy 0.399245 -1.630819) (xy 0.374512 -1.62595)
				(xy 0.366934 -1.617229) (xy 0.35391 -1.611172) (xy 0.317042 -1.606718) (xy 0.259632 -1.604154) (xy 0.211449 -1.603639)
				(xy 0.145912 -1.604778) (xy 0.09333 -1.607915) (xy 0.058786 -1.612627) (xy 0.047565 -1.617229) (xy 0.028832 -1.627749)
				(xy 0.005993 -1.630819) (xy -0.019166 -1.635255) (xy -0.027181 -1.643493) (xy -0.03849 -1.656907)
				(xy -0.057752 -1.665871) (xy -0.083611 -1.681034) (xy -0.116459 -1.709076) (xy -0.149575 -1.742986)
				(xy -0.176238 -1.775756) (xy -0.182386 -1.786975) (xy 0.340051 -1.786975) (xy 0.346404 -1.765131)
				(xy 0.348814 -1.762191) (xy 0.361233 -1.754127) (xy 0.366267 -1.766687) (xy 0.366934 -1.787106)
				(xy 0.362282 -1.812646) (xy 0.353344 -1.821081) (xy 0.34272 -1.810245) (xy 0.340051 -1.786975) (xy -0.182386 -1.786975)
				(xy -0.189729 -1.800375) (xy -0.190263 -1.804087) (xy -0.198844 -1.819879) (xy -0.203853 -1.821081)
				(xy -0.213047 -1.832977) (xy -0.217391 -1.86201) (xy -0.217443 -1.865929) (xy -0.221711 -1.901459)
				(xy -0.232021 -1.925337) (xy -0.232434 -1.925767) (xy -0.238911 -1.947226) (xy -0.240035 -1.988002)
				(xy -0.236759 -2.03819) (xy 0.220145 -2.03819) (xy 0.222069 -2.018889) (xy 0.233178 -1.999319) (xy 0.240689 -2.00561)
				(xy 0.243746 -2.036582) (xy 0.243703 -2.048716) (xy 0.242502 -2.075897) (xy 0.287013 -2.075897)
				(xy 0.288276 -2.032847) (xy 0.293356 -2.004785) (xy 0.298983 -1.997753) (xy 0.306848 -1.985555)
				(xy 0.311755 -1.954467) (xy 0.312573 -1.932067) (xy 0.314531 -1.8915) (xy 0.319503 -1.862865) (xy 0.322766 -1.856102)
				(xy 0.332839 -1.856351) (xy 0.338294 -1.877081) (xy 0.338108 -1.911834) (xy 0.335198 -1.934785)
				(xy 0.328873 -1.968308) (xy 0.500095 -1.968308) (xy 0.500115 -1.933394) (xy 0.503712 -1.903571)
				(xy 0.510232 -1.889221) (xy 0.511173 -1.889032) (xy 0.513875 -1.901291) (xy 0.515184 -1.932781)
				(xy 0.515071 -1.96038) (xy 0.51337 -1.998332) (xy 0.509952 -2.010521) (xy 0.50442 -1.998332) (xy 0.504307 -1.99793)
				(xy 0.500095 -1.968308) (xy 0.328873 -1.968308) (xy 0.328403 -1.970801) (xy 0.317999 -2.021246)
				(xy 0.308336 -2.065704) (xy 0.294695 -2.12686) (xy 0.479542 -2.12686) (xy 0.480406 -2.09463) (xy 0.482828 -2.08285)
				(xy 0.485222 -2.0893) (xy 0.487669 -2.126583) (xy 0.485407 -2.157251) (xy 0.482293 -2.166682) (xy 0.480153 -2.151993)
				(xy 0.479542 -2.12686) (xy 0.294695 -2.12686) (xy 0.288633 -2.15404) (xy 0.287013 -2.075897) (xy 0.242502 -2.075897)
				(xy 0.242326 -2.079889) (xy 0.238364 -2.086841) (xy 0.229673 -2.072526) (xy 0.228371 -2.069852)
				(xy 0.220145 -2.03819) (xy -0.236759 -2.03819) (xy -0.23658 -2.040932) (xy -0.229323 -2.098854)
				(xy -0.219039 -2.154604) (xy -0.206502 -2.20102) (xy -0.205846 -2.202742) (xy 0.034363 -2.202742)
				(xy 0.034789 -2.171897) (xy 0.040103 -2.144994) (xy 0.049038 -2.133655) (xy 0.052203 -2.14577) (xy 0.053868 -2.176234)
				(xy 0.053947 -2.191413) (xy 0.052414 -2.225283) (xy 0.047692 -2.234987) (xy 0.039969 -2.225902)
				(xy 0.034363 -2.202742) (xy -0.205846 -2.202742) (xy -0.201105 -2.215196) (xy -0.184815 -2.250304)
				(xy 0.313646 -2.250304) (xy 0.316145 -2.232677) (xy 0.320784 -2.232467) (xy 0.324028 -2.250655)
				(xy 0.321857 -2.258514) (xy 0.315822 -2.263662) (xy 0.313646 -2.250304) (xy -0.184815 -2.250304)
				(xy -0.165606 -2.291705) (xy -0.15484 -2.310327) (xy 0 -2.310327) (xy 0.003936 -2.281701) (xy 0.013421 -2.269559)
				(xy 0.01359 -2.269556) (xy 0.023132 -2.281366) (xy 0.027179 -2.30982) (xy 0.02718 -2.310327) (xy 0.023243 -2.338953)
				(xy 0.013759 -2.351094) (xy 0.01359 -2.351097) (xy 0.004048 -2.339288) (xy 0.000001 -2.310834) (xy 0 -2.310327)
				(xy -0.15484 -2.310327) (xy -0.135377 -2.343993) (xy -0.118914 -2.365036) (xy -0.10074 -2.388306)
				(xy -0.094768 -2.401492) (xy -0.083648 -2.423849) (xy -0.055342 -2.455281) (xy -0.047357 -2.462414)
				(xy 0.19047 -2.462414) (xy 0.192599 -2.419916) (xy 0.198834 -2.399375) (xy 0.203852 -2.398663) (xy 0.213268 -2.416873)
				(xy 0.217235 -2.449252) (xy 0.217234 -2.450428) (xy 0.213093 -2.487632) (xy 0.203852 -2.514179)
				(xy 0.285393 -2.514179) (xy 0.290365 -2.502993) (xy 0.294453 -2.505119) (xy 0.296079 -2.521247)
				(xy 0.294453 -2.523239) (xy 0.286374 -2.521374) (xy 0.285393 -2.514179) (xy 0.203852 -2.514179)
				(xy 0.195942 -2.518391) (xy 0.191649 -2.499148) (xy 0.19047 -2.462414) (xy -0.047357 -2.462414)
				(xy -0.015803 -2.490603) (xy 0.029015 -2.524628) (xy 0.07316 -2.552171) (xy 0.085283 -2.558347)
				(xy 0.133963 -2.578965) (xy 0.178897 -2.590432) (xy 0.232004 -2.595141) (xy 0.271302 -2.59572)
			)
			(stroke
				(width 0)
				(type solid)
			)
			(fill yes)
			(layer "F.Cu")
			(uuid "61955f57-efa1-4ac5-92ed-3ff84f29cc7e")
		)
		(fp_poly
			(pts
				(xy 2.292897 -2.848419) (xy 2.342628 -2.845002) (xy 2.381247 -2.838914) (xy 2.401487 -2.83028) (xy 2.402678 -2.828294)
				(xy 2.418221 -2.818337) (xy 2.450094 -2.813153) (xy 2.457553 -2.812954) (xy 2.487886 -2.81111) (xy 2.493684 -2.805185)
				(xy 2.486998 -2.799572) (xy 2.477805 -2.790153) (xy 2.492094 -2.786492) (xy 2.503986 -2.78619) (xy 2.531112 -2.781773)
				(xy 2.541359 -2.772392) (xy 2.55241 -2.760441) (xy 2.562393 -2.758802) (xy 2.585488 -2.749468) (xy 2.61305 -2.7268)
				(xy 2.614914 -2.724827) (xy 2.642697 -2.70146) (xy 2.667353 -2.690903) (xy 2.668626 -2.690851) (xy 2.68787 -2.684623)
				(xy 2.69085 -2.678428) (xy 2.699374 -2.661875) (xy 2.721007 -2.633964) (xy 2.735018 -2.618134) (xy 2.775826 -2.573125)
				(xy 2.800399 -2.543838) (xy 2.811626 -2.526682) (xy 2.813162 -2.52093) (xy 2.821525 -2.506512) (xy 2.841847 -2.48228)
				(xy 2.84374 -2.48024) (xy 2.87864 -2.441666) (xy 2.898252 -2.415557) (xy 2.906731 -2.395386) (xy 2.908293 -2.378851)
				(xy 2.913878 -2.356458) (xy 2.921883 -2.351097) (xy 2.932796 -2.339674) (xy 2.935473 -2.322946)
				(xy 2.944798 -2.290005) (xy 2.955858 -2.27441) (xy 2.972347 -2.244735) (xy 2.976244 -2.222153) (xy 2.981422 -2.195627)
				(xy 2.990102 -2.185661) (xy 2.995407 -2.170842) (xy 2.996401 -2.135633) (xy 2.99383 -2.086194) (xy 2.988441 -2.028689)
				(xy 2.980979 -1.969277) (xy 2.972193 -1.914121) (xy 2.962828 -1.869382) (xy 2.95363 -1.841222) (xy 2.947576 -1.834671)
				(xy 2.937666 -1.823302) (xy 2.935473 -1.808088) (xy 2.926049 -1.785864) (xy 2.901675 -1.752666)
				(xy 2.868196 -1.714594) (xy 2.831461 -1.67775) (xy 2.797315 -1.648234) (xy 2.771606 -1.632148) (xy 2.765599 -1.630819)
				(xy 2.747512 -1.623482) (xy 2.745211 -1.617229) (xy 2.733829 -1.606187) (xy 2.718031 -1.603639)
				(xy 2.695947 -1.597947) (xy 2.69085 -1.590049) (xy 2.679309 -1.579523) (xy 2.659593 -1.576458) (xy 2.629347 -1.571655)
				(xy 2.615425 -1.564547) (xy 2.594763 -1.557422) (xy 2.553414 -1.55137) (xy 2.49786 -1.546802) (xy 2.434587 -1.544127)
				(xy 2.370078 -1.543756) (xy 2.317121 -1.54568) (xy 2.271415 -1.55042) (xy 2.236581 -1.557481) (xy 2.222669 -1.563614)
				(xy 2.200482 -1.57313) (xy 2.171522 -1.576458) (xy 2.134159 -1.58071) (xy 2.109687 -1.588542) (xy 2.082557 -1.60214)
				(xy 2.044543 -1.620875) (xy 2.034231 -1.625915) (xy 1.989045 -1.652698) (xy 1.944596 -1.686062)
				(xy 1.937912 -1.691975) (xy 1.904057 -1.729411) (xy 1.870697 -1.776693) (xy 1.842688 -1.825649)
				(xy 1.824884 -1.868103) (xy 1.82108 -1.888712) (xy 1.814729 -1.914527) (xy 1.80749 -1.923007) (xy 1.798628 -1.940914)
				(xy 1.794065 -1.974424) (xy 1.7939 -1.982469) (xy 1.791514 -2.026538) (xy 1.785454 -2.080794) (xy 1.781428 -2.107376)
				(xy 1.77152 -2.17389) (xy 1.764277 -2.238088) (xy 1.764147 -2.23981) (xy 1.847244 -2.23981) (xy 1.847723 -2.150469)
				(xy 1.852541 -2.064626) (xy 1.861683 -1.989863) (xy 1.872916 -1.940455) (xy 1.887398 -1.897357)
				(xy 1.900063 -1.865302) (xy 1.906691 -1.853252) (xy 1.915483 -1.832299) (xy 1.916211 -1.824029)
				(xy 1.926009 -1.803509) (xy 1.950591 -1.77394) (xy 1.98274 -1.742236) (xy 2.01524 -1.715306) (xy 2.040874 -1.700065)
				(xy 2.046998 -1.69877) (xy 2.063978 -1.690864) (xy 2.065703 -1.68518) (xy 2.077234 -1.674405) (xy 2.096281 -1.671157)
				(xy 2.131813 -1.6626) (xy 2.153239 -1.650772) (xy 2.187907 -1.63484) (xy 2.214395 -1.630611) (xy 2.249411 -1.625432)
				(xy 2.269556 -1.617229) (xy 2.294642 -1.610279) (xy 2.339222 -1.605971) (xy 2.395741 -1.604265)
				(xy 2.456646 -1.605118) (xy 2.514384 -1.608488) (xy 2.561399 -1.614333) (xy 2.581164 -1.618961)
				(xy 2.62506 -1.634871) (xy 2.664482 -1.652278) (xy 2.665767 -1.652937) (xy 2.698024 -1.666545) (xy 2.720525 -1.671589)
				(xy 2.742285 -1.681668) (xy 2.758801 -1.69877) (xy 2.778048 -1.719664) (xy 2.789952 -1.72595) (xy 2.810478 -1.736081)
				(xy 2.831192 -1.75817) (xy 2.840342 -1.77934) (xy 2.850113 -1.793312) (xy 2.853932 -1.793901) (xy 2.864974 -1.805283)
				(xy 2.867522 -1.821081) (xy 2.872704 -1.843173) (xy 2.879885 -1.848262) (xy 2.888032 -1.860591)
				(xy 2.897919 -1.893062) (xy 2.90752 -1.938895) (xy 2.908293 -1.943393) (xy 2.916998 -2.017098) (xy 2.915095 -2.08472)
				(xy 2.908301 -2.133607) (xy 2.898734 -2.181663) (xy 2.888709 -2.218313) (xy 2.880307 -2.236033)
				(xy 2.879893 -2.236335) (xy 2.870332 -2.254425) (xy 2.867522 -2.277153) (xy 2.863923 -2.302323)
				(xy 2.85725 -2.310327) (xy 2.845513 -2.321472) (xy 2.830006 -2.348861) (xy 2.827428 -2.354495) (xy 2.809686 -2.390828)
				(xy 2.789534 -2.420563) (xy 2.762199 -2.452524) (xy 2.747813 -2.472528) (xy 2.745211 -2.479902)
				(xy 2.735737 -2.494888) (xy 2.710836 -2.522456) (xy 2.675791 -2.557586) (xy 2.635883 -2.595256)
				(xy 2.596397 -2.630444) (xy 2.562613 -2.658131) (xy 2.544275 -2.670905) (xy 2.515854 -2.690275)
				(xy 2.501149 -2.705338) (xy 2.500588 -2.707371) (xy 2.488942 -2.715389) (xy 2.466613 -2.718031)
				(xy 2.441065 -2.722198) (xy 2.432637 -2.730194) (xy 2.420129 -2.739924) (xy 2.386927 -2.748952)
				(xy 2.339512 -2.756145) (xy 2.284368 -2.760374) (xy 2.255965 -2.761023) (xy 2.200807 -2.758797)
				(xy 2.151014 -2.752593) (xy 2.11321 -2.743667) (xy 2.094021 -2.733274) (xy 2.092883 -2.730135) (xy 2.081854 -2.71939)
				(xy 2.072498 -2.718031) (xy 2.052585 -2.708847) (xy 2.022706 -2.685837) (xy 1.990052 -2.655813)
				(xy 1.961815 -2.625588) (xy 1.945185 -2.601973) (xy 1.943392 -2.59572) (xy 1.93305 -2.582525) (xy 1.929802 -2.58213)
				(xy 1.918605 -2.570799) (xy 1.916211 -2.556082) (xy 1.911606 -2.532279) (xy 1.906019 -2.525504)
				(xy 1.896131 -2.511116) (xy 1.881773 -2.479099) (xy 1.871976 -2.453023) (xy 1.859357 -2.398668)
				(xy 1.851117 -2.32507) (xy 1.847244 -2.23981) (xy 1.764147 -2.23981) (xy 1.759984 -2.294918) (xy 1.758925 -2.339327)
				(xy 1.761385 -2.366262) (xy 1.76654 -2.371594) (xy 1.775346 -2.377937) (xy 1.779879 -2.407971) (xy 1.78031 -2.426012)
				(xy 1.785085 -2.473711) (xy 1.797845 -2.506003) (xy 1.800695 -2.509325) (xy 1.817565 -2.539406)
				(xy 1.82108 -2.559715) (xy 1.831514 -2.590825) (xy 1.848261 -2.60931) (xy 1.869312 -2.630903) (xy 1.875441 -2.646286)
				(xy 1.885911 -2.662461) (xy 1.892429 -2.663879) (xy 1.899503 -2.668577) (xy 1.889031 -2.677261)
				(xy 1.87745 -2.688063) (xy 1.886251 -2.690643) (xy 1.907734 -2.699433) (xy 1.935451 -2.720401) (xy 1.93656 -2.721429)
				(xy 1.976103 -2.757277) (xy 2.001911 -2.777323) (xy 2.019129 -2.785317) (xy 2.025161 -2.785982)
				(xy 2.033811 -2.794274) (xy 2.031728 -2.799572) (xy 2.037104 -2.809139) (xy 2.063739 -2.813148)
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
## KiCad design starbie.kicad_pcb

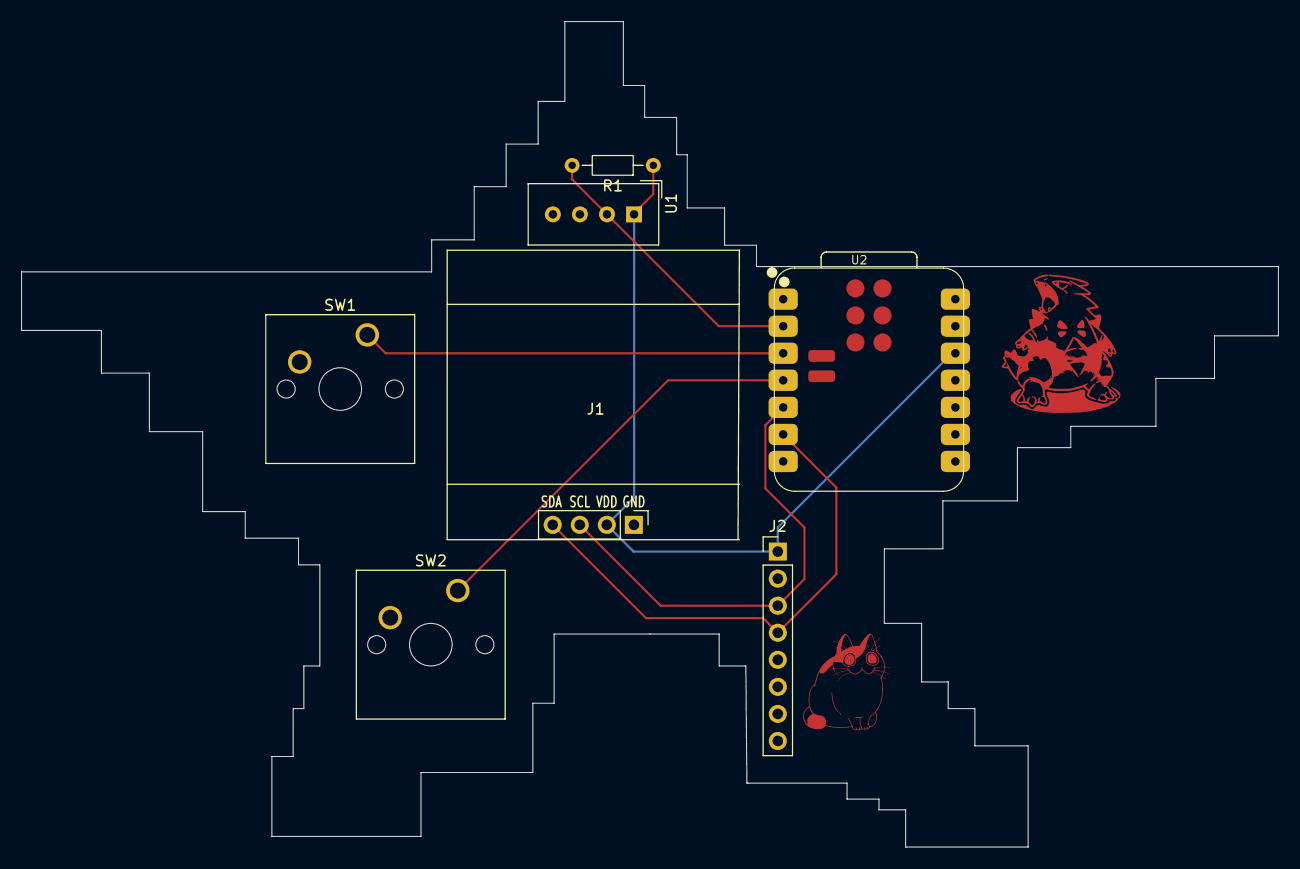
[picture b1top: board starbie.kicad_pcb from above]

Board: 2 copper layers, 118.0 x 77.5 mm, 7 parts (0 on the bottom side), 7 nets.

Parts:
J1: Conn_01x04_Pin; Display_128x64_096_I2C
J2: Conn_01x08_Pin; PinHeader_1x08_P2.54mm_Vertical
R1: 10k; R_Axial_DIN0204_L3.6mm_D1.6mm_P7.62mm_Horizontal
SW1, SW2: SW_Push; SW_Cherry_MX_1.00u_PCB
U1: DHT11; Aosong_DHT11_5.5x12.0_P2.54mm
U2: XIAO-ESP32-S3-SMD; XIAO-ESP32-C3-SMD

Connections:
+3.3V: J1.2, J2.1, R1.1, U1.1 (VDD), U2.12 (3V3_OUT)
/DHT11 DATA: R1.2, U1.2 (DATA), U2.2 (D1)
/GPIO2: SW1.1, U2.3 (D2)
/GPIO3: SW2.1, U2.4 (D3)
/SCL: J1.3, J2.3, U2.5 (D4)
/SDA: J1.4, J2.4, U2.6 (D5)
GND: J1.1, J2.2, SW1.2, SW2.2, U1.4 (GND), U2.13 (GND), U2.18 (GND)
